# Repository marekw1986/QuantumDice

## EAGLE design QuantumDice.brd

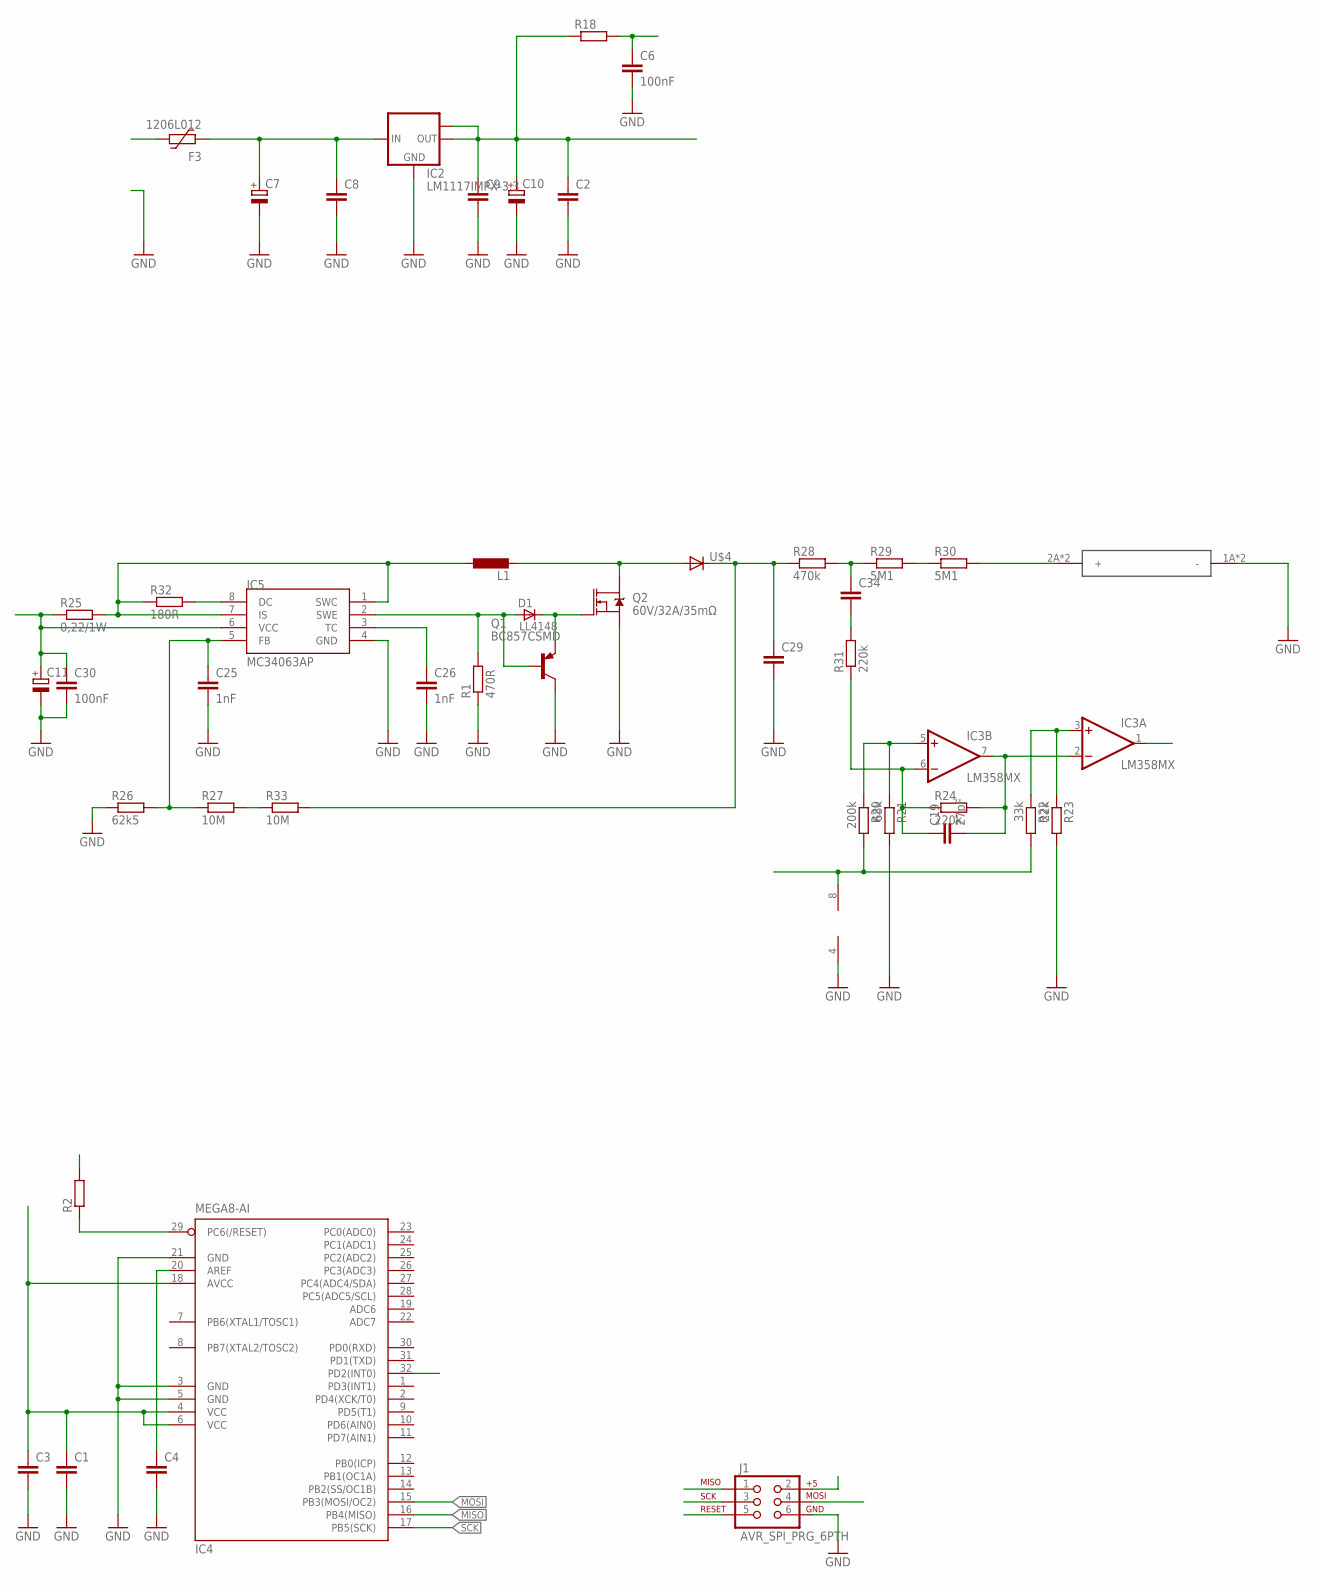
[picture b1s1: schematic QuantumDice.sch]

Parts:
C1, C2, C3, C4: C-EUC0603; C0603
C6, C30: 100nF; C0603
C7, C10: CPOL-EUSMCC; SMC_C
C8, C9: C-EUC1206; C1206
C11: CPOL-EUSMCE; SMC_E
C19: 27pF; C0603
C25, C26: 1nF; C0603
C29: C-EU225-113X268; C225-113X268
C34: C-EU050-024X044; C050-024X044
D1: LL4148; SOD80_DO213AA_MINIMELF
F3: 1206L012; 1206L
IC2: LM1117IMPX-3.3; SOT223
IC3: LM358MX; SO08
IC4: MEGA8-AI; TQFP32-08
IC5: MC34063AP; DIL08
J1: AVR_SPI_PRG_6PTH; 2X3
L1: L-EU6000-XXX-RC; 6000-XXXX-RC
Q1: BC857CSMD; SOT23-BEC
Q2: 60V/32A/35mΩ; TO220V
R1: 470R; R1206
R2: R-EU_R0603; R0603
R18: R-EU_R1206; R1206
R20: 200k; R0603
R21: 68k; R0603
R22: 33k; R1206
R23: 22k; R0603
R24: 220k; R0603
R25: 0,22/1W; R2010
R26: 62k5; R1206
R27, R33: 10M; R2512
R28: 470k; R2512
R29, R30: 5M1; R2512
R31: 220k; R0805
R32: 180R; R0805
U$4: DIODE-MELF-MLL41; MELF-MLL41
U$5: STS5; GEIGERTUBE

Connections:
9V: C7.+, C8.1, C11.+, C30.1, F3.2, IC2.3 (IN), IC5.6 (VCC), R25.1
A_5V: C6.1, IC3.8 (V+), R18.2, R20.2, R22.2
CPM: IC3.1 (OUT), IC4.32 (PD2(INT0))
GND: C1.2, C2.2, C3.2, C4.2, C6.2, C7.-, C8.2, C9.2, C10.-, C11.-, C25.2, C26.2, C29.2, C30.2, IC2.1 (GND), IC3.4 (V-), IC4.3 (GND), IC4.5 (GND), IC4.21 (GND), IC5.4 (GND), J1.6, Q1.C, Q2.3 (S), R1.1, R21.2, R23.2, R26.1, U$5.1A (-), U$5.1B (-)
HV: C29.1, R28.1, R33.2, U$4.C
MISO: IC4.16 (PB4(MISO)), J1.1
MOSI: IC4.15 (PB3(MOSI/OC2)), J1.4
unnamed: D1.A, IC5.2 (SWE), Q1.B, R1.2
unnamed: D1.C, Q1.E, Q2.1 (G)
unnamed: C19.1, IC3.6 (-IN), R24.1, R31.1
unnamed: C4.1, IC4.20 (AREF)
unnamed: C19.2, IC3.2 (-IN), IC3.7 (OUT), R24.2
unnamed: C26.1, IC5.3 (TC)
unnamed: IC3.5 (+IN), R20.1, R21.1
unnamed: IC3.3 (+IN), R22.1, R23.1
unnamed: L1.2, Q2.2 (D), U$4.A
unnamed: C25.1, IC5.5 (FB), R26.2, R27.1
unnamed: R30.2, U$5.2A (+), U$5.2B (+)
unnamed: R29.2, R30.1
unnamed: C34.1, R28.2, R29.1
unnamed: C34.2, R31.2
unnamed: IC5.1 (SWC), IC5.7 (IS), L1.1, R25.2, R32.1
unnamed: IC5.8 (DC), R32.2
unnamed: R27.2, R33.1
RESET: IC4.29 (PC6(/RESET)), J1.5, R2.1
SCK: IC4.17 (PB5(SCK)), J1.3
_5V: C1.1, C2.1, C3.1, C9.1, C10.+, IC2.2 (OUT), IC2.TAB (OUT1), IC4.4 (VCC), IC4.6 (VCC), IC4.18 (AVCC), J1.2, R2.2, R18.1

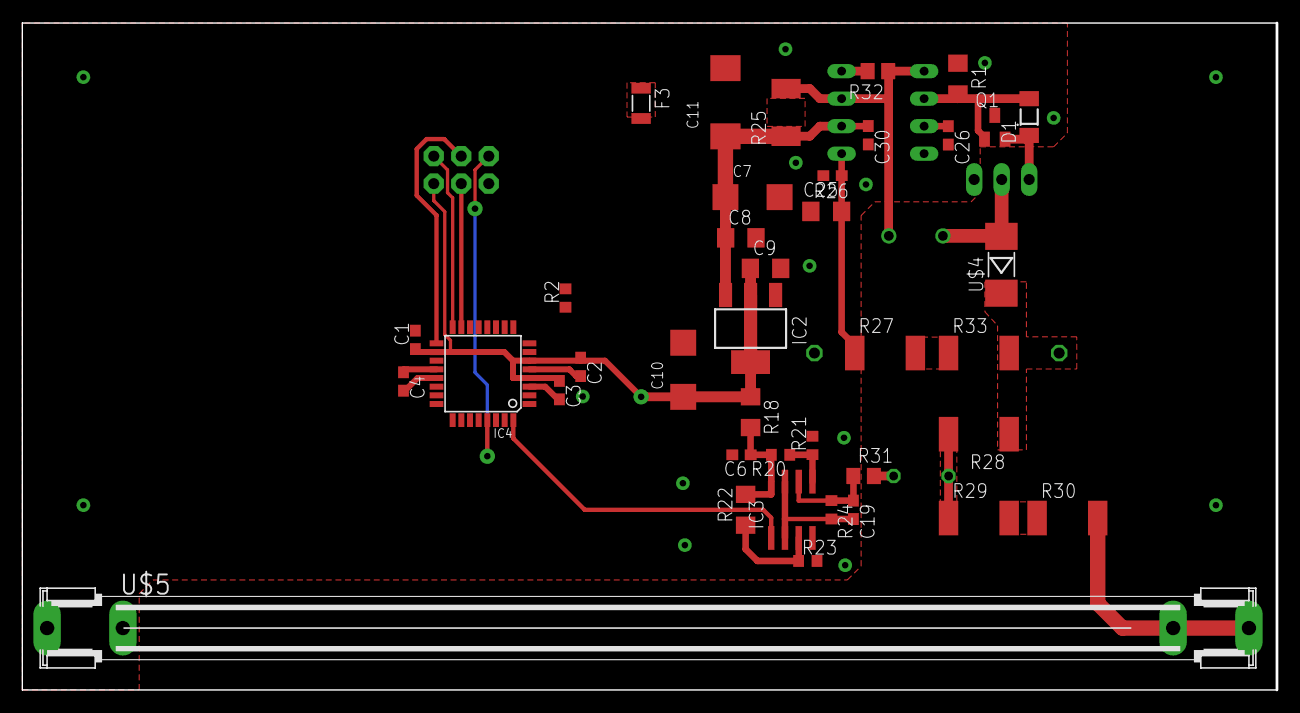
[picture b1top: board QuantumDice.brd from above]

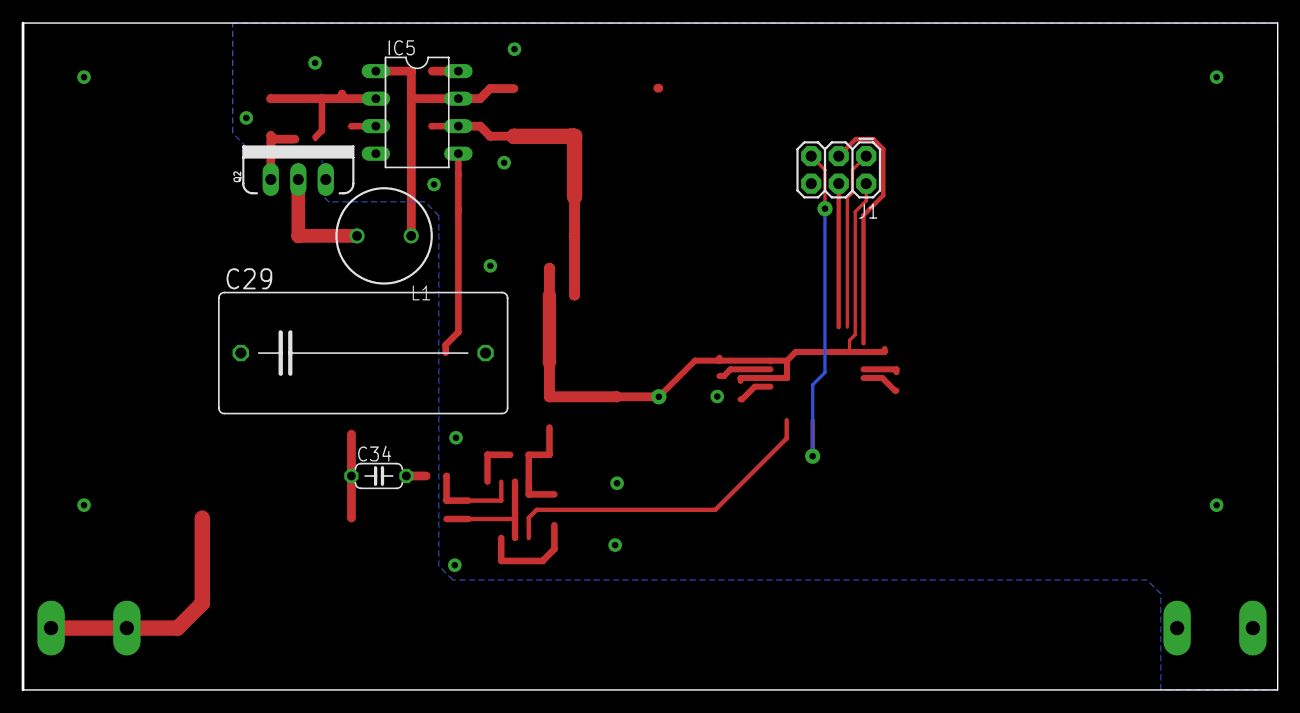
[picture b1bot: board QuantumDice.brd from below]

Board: 2 copper layers, 115.8 x 61.6 mm, 45 parts (6 on the bottom side), 27 nets.

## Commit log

2022-01-17 PCB Added
2022-01-17 PCB updated
2022-11-22 Power circuit updated
2023-09-05 Small updates

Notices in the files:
parts and their libraries:
SparkFun-DiscreteSemi: Licensing: Creative Commons ShareAlike 4.0 International - https://creativecommons.org/licenses/by-sa/4.0
SparkFun-Connectors: Licensing: CC v3.0 Share-Alike You are welcome to use this library for commercial purposes.
